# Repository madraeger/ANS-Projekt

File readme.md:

# FM-VCO

Dieses Repository enthält die Entwicklung, Simulation und praktische Umsetzung eines spannungsgesteuerten Oszillators für einen Frequenzmodulator.

Der VCO wird in **KiCad** aufgebaut und mit **ngspice** simuliert. Anschließend soll die Schaltung auf einer Platine umgesetzt und messtechnisch untersucht werden.

## Kundenanforderungen

Für den Frequenzmodulator wurden folgende Anforderungen vorgegeben:

- Mittenfrequenz von **5,5 MHz**
- Eingangssignal von **0 V**
- lineare Frequenzänderung von **±0,5 MHz**
- nutzbarer Frequenzbereich von **5 MHz bis 6 MHz**
- möglichst geringe nichtlineare Verzerrungen
- robuste und übersichtliche Platine für den Einsatz im Unterricht
- Verwendung möglichst großer und gut handhabbarer Bauteile
- integrierter Spannungsteiler zur Einstellung des Arbeitspunktes
- Ein- und Ausgang über BNC-Buchsen
- Ausgangswiderstand von **50 Ω**
- Korrektur einer Frequenzdrift über eine einstellbare Gleichspannung
- Aufnahme der Frequenzkennlinie mithilfe einer Gleichspannung
- möglichst kurzschlusssicherer Ausgang

## Grundlagen und Aufbau des VCOs

### Vom Schwingkreis zum Oszillator

Die Grundlage des VCOs bildet ein LC-Schwingkreis aus Induktivitäten und Kapazitäten. Im Schwingkreis wird Energie periodisch zwischen dem magnetischen Feld der Induktivitäten und dem elektrischen Feld der Kapazitäten ausgetauscht.

Die Resonanzfrequenz kann näherungsweise mit

$$
f_0 \approx \frac{1}{2\pi\sqrt{L_\text{}C_\text{}}}
$$

beschrieben werden.

Dabei sind:

- $L_\text{}$ die wirksame Induktivität des Schwingkreises
- $C_\text{}$ die gesamte wirksame Kapazität einschließlich parasitärer Kapazitäten

Ein realer LC-Schwingkreis besitzt Verluste, beispielsweise durch die Innenwiderstände der Induktivitäten, Leiterbahnen und angeschlossene Messgeräte. Ohne zusätzliche Energiezufuhr würde die Schwingung deshalb mit der Zeit abklingen.

Damit eine dauerhafte Schwingung entsteht, muss eine aktive Schaltung die Verluste des Schwingkreises ausgleichen. Dazu wird ein Teil des Ausgangssignals phasenrichtig zurückgeführt und verstärkt. Beim Einschalten reichen bereits kleine Störungen und das elektrische Rauschen aus, um eine Schwingung anzuregen. Die Frequenzanteile in der Nähe der Resonanzfrequenz werden anschließend durch die Rückkopplung verstärkt.

Für das Anschwingen muss die Schleifenverstärkung zunächst ausreichend groß sein. Im eingeschwungenen Zustand stellt sich die Amplitude so ein, dass die zugeführte Energie den Verlusten des Schwingkreises entspricht.

### Aufbau des VCOs

Der verwendete VCO besteht grundsätzlich aus einem differentiellen LC-Schwingkreis, einem gekreuzt gekoppelten MOSFET-Paar und einer Stromquelle.

<p align="center">
  <em>
    Vereinfachter Aufbau eines differentiellen LC-VCOs.
    Quelle:
    <a href="https://analogcircuitdesign.com/voltage-controlled-oscillator/">
      Analog Circuit Design
    </a>
  </em>
</p>

Der VCO setzt sich aus folgenden Funktionsgruppen zusammen:

| Funktionsgruppe | Bauteile der Prinzipschaltung | Bauteile der aktuellen Schaltung | Aufgabe |
|---|---|---|---|
| LC-Schwingkreis | `L1`, `L2`, `C1`, `C2` sowie die Verlustwiderstände `R1`, `R2` | `L1`, `L2`, `D1`, `D2` | Festlegung der Resonanzfrequenz |
| Cross-Coupled-Paar | `M1`, `M2` | `Q1`, `Q2` | Ausgleich der Schwingkreisverluste und Aufrechterhaltung der Schwingung |
| Frequenzabstimmung | Varaktordioden und Steuerspannung `Vctrl` | `D1`, `D2` und Abstimmspannung `Vtune` | Veränderung der wirksamen Kapazität und damit der Ausgangsfrequenz |
| Stromquelle | ideale Stromquelle `Idc` | `Q3`, `Q4`, `R4` | Einstellung und Begrenzung des Arbeitspunktstroms |
| Ausgang | einer der beiden Schwingkreisknoten | rechter Schwingkreisknoten | Ausgabe des hochfrequenten Signals |

In der Prinzipschaltung werden die Verluste des LC-Schwingkreises durch die Parallelwiderstände `R1` und `R2` dargestellt. In der realen Schaltung entstehen diese Verluste bereits durch die Innenwiderstände der Spulen, die Varaktordioden, die MOSFETs und die Leiterbahnen. Deshalb wurden keine zusätzlichen Widerstände parallel zum Schwingkreis eingesetzt.

Die Kondensatoren `C1` und `C2` der Prinzipschaltung werden in der aktuellen Schaltung hauptsächlich durch die spannungsabhängigen Kapazitäten der Varaktordioden `D1` und `D2` ersetzt.

Der LC-Schwingkreis bestimmt die Ausgangsfrequenz. Das Cross-Coupled-Transistorpaar führt dem Schwingkreis die durch reale Verluste abgegebene Energie wieder zu. Die Varaktordioden ermöglichen die spannungsabhängige Frequenzeinstellung über `Vtune`.

Als Stromquelle wird ein einfacher NMOS-Stromspiegel verwendet. Dieser stellt den Arbeitspunktstrom für das Cross-Coupled-Transistorpaar bereit.

Die einzelnen Funktionsgruppen werden in den folgenden Abschnitten genauer beschrieben.
### Cross-Coupled-Transistorpaar

Die MOSFETs `Q1` und `Q2` sind über Kreuz miteinander gekoppelt. Das Gate eines Transistors ist jeweils mit dem Drain des anderen Transistors verbunden.

Die beiden Schwingkreisknoten schwingen dadurch näherungsweise gegenphasig. Steigt die Spannung an einem Knoten an, fällt sie am anderen Knoten ab.

Das Transistorpaar erzeugt im Schwingkreis einen negativen differentiellen Widerstand. Dieser wirkt den realen Verlustwiderständen des Schwingkreises entgegen. Sind die Verluste ausreichend kompensiert, kann die Schwingung dauerhaft bestehen bleiben.

### Spannungsabhängige Frequenzabstimmung

Damit aus dem LC-Oszillator ein spannungsgesteuerter Oszillator wird, werden die festen Kapazitäten durch Varaktordioden ersetzt.

Eine Varaktordiode wird in Sperrrichtung betrieben und verhält sich dabei wie ein spannungsabhängiger Kondensator. Die Abstimmspannung `Vtune` verändert die Sperrspannung und damit die Kapazität der Dioden.

Dadurch verändert sich die wirksame Kapazität des Schwingkreises:

$$
V_\text{tune}
\longrightarrow
C_\text{Varaktor}
\longrightarrow
f_\text{out}
$$

In der aktuellen Schaltung nimmt die gemessene Ausgangsfrequenz mit zunehmender Spannung `Vtune` ab. Die genaue Richtung der Frequenzänderung hängt von der Verschaltung der Varaktordioden und den Spannungsverhältnissen innerhalb des Schwingkreises ab.

Für einen möglichst verzerrungsarmen Frequenzmodulator sollte der Zusammenhang zwischen Abstimmspannung und Ausgangsfrequenz im verwendeten Arbeitsbereich möglichst linear sein:

$$
f_\text{out}
\approx
f_\text{Mitte}
+
K_\text{VCO}\cdot\left(V_\text{tune}-V_\text{Mitte}\right)
$$

Dabei beschreibt $K_\text{VCO}$ die Empfindlichkeit des VCOs und wird beispielsweise in `MHz/V` angegeben.

### NMOS-Stromspiegel

Die Stromquelle des VCOs wird als einfacher NMOS-Stromspiegel ausgeführt.

<p align="center">
  <em>
    Prinzip eines einfachen NMOS-Stromspiegels.
    Quelle:
    <a href="https://www.allaboutcircuits.com/technical-articles/the-basic-mosfet-constant-current-source/">
      All About Circuits
    </a>
  </em>
</p>

Der Stromspiegel besteht in der aktuellen Schaltung aus den MOSFETs `Q3` und `Q4` sowie dem Widerstand `R4`.

Bei `Q4` sind Gate und Drain miteinander verbunden. Der Transistor ist damit als Referenztransistor beschaltet. Über den Widerstand `R4` stellt sich ein Referenzstrom ein.

Da die Gates von `Q3` und `Q4` miteinander verbunden sind, liegt an beiden MOSFETs näherungsweise dieselbe Gate-Source-Spannung an. Dadurch übernimmt `Q3` näherungsweise den Strom des Referenzzweigs und stellt den Arbeitspunktstrom für das Cross-Coupled-Transistorpaar bereit.

Die Bauteile der Prinzipschaltung entsprechen in der aktuellen VCO-Schaltung folgenden Bauteilen:

| Prinzipschaltung | Aktuelle Schaltung |
|---|---|
| Referenztransistor `Q1` | `Q4` |
| Ausgangstransistor `Q2` | `Q3` |
| Einstellwiderstand `RSET` | `R4` |
| Referenzstrom `IREF` | Strom durch `R4` und `Q4` |
| Ausgangsstrom `IBIAS` | Arbeitspunktstrom für `Q1` und `Q2` |

Der Referenzstrom kann vereinfacht mit folgender Gleichung abgeschätzt werden:

$$
I_\text{REF}
\approx
\frac{V_\text{DD}-V_\text{GS}}{R_4}
$$

Diese Gleichung ist nur eine Näherung, da die Gate-Source-Spannung `VGS` vom verwendeten MOSFET, vom Strom und von der Temperatur abhängt.

Der Stromspiegel stabilisiert damit den Arbeitspunkt der Schaltung, stellt jedoch keine vollständige automatische Regelung der Ausgangsamplitude dar.

## Verwendete Bauteile

Für den aktuellen Aufbau werden unter anderem folgende Bauteile verwendet:

| Bezeichnung | Bauteil | Funktion | SPICE-Modell / Bibliothek | Datenblatt |
|---|---|---|---|---|
| Q1, Q2 | [`BS170`](https://www.onsemi.com/download/data-sheet/pdf/mmbf170-d.pdf) | Cross-Coupled-Transistorpaar | `elk.lib` |  |
| Q3, Q4 | [`BS170`](https://www.onsemi.com/download/data-sheet/pdf/mmbf170-d.pdf) | NMOS-Stromspiegel | `elk.lib` |  |
| D1, D2 | [`1SV149`](https://www.radiomuseum.co.uk/filter/1SV149.pdf) | Varaktordioden zur Frequenzabstimmung | `BB112.lib` beziehungsweise eigenes `1SV149`-Modell |  |
| L1, L2 | 3,3 µH | Induktiver Teil des Schwingkreises | Standardmodell aus `spice.lib` | – |
| R4 | 51 kΩ | Einstellung des Referenzstroms im realen Aufbau | Standardmodell aus `spice.lib` | – |

Für die MOSFETs wird das Modell des `BS170` aus der Bibliothek `elk.lib` verwendet. Die passiven Bauteile greifen auf die Standardmodelle aus `spice.lib` zurück.

Für die Varaktordioden wurde zunächst das Modell aus `BB112.lib` verwendet, da damit in der Simulation eine deutliche Frequenzänderung erreicht werden konnte. Alternativ wird ein eigenes Modell für die `1SV149` eingesetzt. Das Modell aus `BB112.lib` entspricht dabei nicht exakt der real verbauten `1SV149`, sondern dient lediglich als Näherung ihres kapazitätsabhängigen Verhaltens.

## Aktueller Stand

Der VCO wurde sowohl in **SPICE simuliert** als auch **praktisch aufgebaut**. Der geforderte nutzbare Frequenzbereich von ungefähr **5 MHz bis 6 MHz** wird bereits erreicht.

Die Ausgangsfrequenz wird über die Abstimmspannung `Vtune` eingestellt. Mit steigender Abstimmspannung sinkt die Ausgangsfrequenz. Die aufgenommenen Messwerte zeigen dabei einen nahezu linearen Zusammenhang zwischen `Vtune` und der Ausgangsfrequenz.

### Gemessene f/V-Kennlinie

Die Kennlinie wurde aufgenommen, indem die Gleichspannung `Vtune` schrittweise verändert und die jeweilige Ausgangsfrequenz gemessen wurde.

| `Vtune` in V | Frequenz in MHz |
|---:|---:|
| 5,33 | 6,00 |
| 5,50 | 5,90 |
| 5,63 | 5,83 |
| 5,82 | 5,69 |
| 5,92 | 5,61 |
| 6,06 | 5,52 |
| 6,24 | 5,42 |
| 6,36 | 5,33 |
| 6,54 | 5,21 |
| 6,70 | 5,11 |
| 6,89 | 5,01 |

<p align="center">
  <em>Gemessene Ausgangsfrequenz in Abhängigkeit von der Abstimmspannung Vtune</em>
</p>

Die VCO-Empfindlichkeit beträgt näherungsweise:

$$
K_\text{VCO}
\approx
-0{,}650\,
\frac{\text{MHz}}{\text{V}}
$$

Das negative Vorzeichen bedeutet, dass die Ausgangsfrequenz mit steigender Abstimmspannung abnimmt.

Die Mittenfrequenz von ungefähr **5,5 MHz** wird bei einer Abstimmspannung von etwa **6,1 V** erreicht.

Für den gesamten Frequenzbereich von ungefähr **5 MHz bis 6 MHz** wird eine Spannungsänderung von etwa

$$
\Delta V_\text{tune} = 6{,}89\,\text{V} - 5{,}33\,\text{V} = 1{,}56\,\text{V}
$$

benötigt.

Bezogen auf den Arbeitspunkt bei ungefähr **6,1 V** entspricht dies einem benötigten Spannungshub von ungefähr:

$$
V_\text{tune}
\approx
6{,}1\,\text{V}
\pm
0{,}78\,\text{V}
$$

Der ursprünglich vorgesehene Eingangsspannungsbereich von ungefähr **±0,5 V** reicht daher ohne eine zusätzliche Anpassung nicht für den vollständigen Frequenzbereich aus.

### Gemessene Ausgangssignale

Die folgende Abbildunge zeigt die letzten zwei Perioden des mit dem Oszilloskop aufgenommenen Ausgangssignals.

<p align="center">
  <em>Gemessenes Ausgangssignal bei 5 - 6 MHz</em>
</p>

Die gemessenen Signale besitzen über den untersuchten Frequenzbereich eine weitgehend sinusförmige Signalform.

Die Ausgangsamplitude ist bei **5 MHz** und **5,5 MHz** ähnlich groß. In Richtung **6 MHz** nimmt die Amplitude jedoch sichtbar ab. Die Ursache dafür muss im weiteren Projektverlauf noch untersucht werden.

### Simulation und Vergleich

Für die Frequenzen **5 MHz**, **5,5 MHz** und **6 MHz** wurden die simulierten Ausgangssignale mit den Oszilloskopmessungen verglichen.

<details>
  <summary><strong>Vergleich bei 5 MHz anzeigen</strong></summary>

  #### Vergleich bei 5 MHz

</details>

<details>
  <summary><strong>Vergleich bei 5,5 MHz anzeigen</strong></summary>

  #### Vergleich bei 5,5 MHz

</details>

<details>
  <summary><strong>Vergleich bei 6 MHz anzeigen</strong></summary>

  #### Vergleich bei 6 MHz

</details>

Die normierten Vergleichsplots zeigen, dass Simulation und Messung grundsätzlich eine ähnliche periodische Signalform besitzen.

Die Simulation beschreibt damit das grundsätzliche Schwingverhalten, bildet den realen Arbeitspunkt und die tatsächliche Ausgangsamplitude jedoch nur eingeschränkt ab.

### Unterschiede zwischen Simulation und realem Aufbau

Für den NMOS-Stromspiegel werden in der Simulation und im realen Aufbau unterschiedliche Widerstandswerte benötigt.

Im realen Aufbau wird für `R4` ein Widerstand von **51 kΩ** verwendet. Bei größeren Widerständen ist der Strom zu gering, sodass der Oszillator nicht zuverlässig anschwingt.

In der SPICE-Simulation wird dagegen ein größerer Widerstand benötigt, da kleinere Widerstandswerte dort zu stärkeren Verzerrungen des Ausgangssignals führen.

Zusätzlich wurden im realen Aufbau Kondensatoren parallel zur Spannungsversorgung eingesetzt. Diese dienen als Abblock- und Stützkondensatoren und reduzieren hochfrequente Störungen sowie kurzzeitige Spannungsschwankungen.

### Platinenlayout

Eine erste Platine wurde bereits in KiCad erstellt. Das Layout muss jedoch noch an den aktuellen Schaltungsstand angepasst und weiter optimiert werden.

Besonders berücksichtigt werden müssen:

- Platzierung der Abblockkondensatoren nahe an den MOSFETs
- Ein- und Ausgangsanpassung

## Noch nicht vollständig erfüllte Anforderungen

Der geforderte Frequenzbereich von ungefähr **5 MHz bis 6 MHz** und die Mittenfrequenz von ungefähr **5,5 MHz** werden bereits erreicht. Auch die Frequenzkennlinie wurde mithilfe einer veränderlichen Gleichspannung aufgenommen und zeigt im untersuchten Bereich einen nahezu linearen Verlauf.

Folgende Kundenanforderungen sind noch nicht vollständig erfüllt:

- Anpassung des Eingangs von **0 V**
- Umsetzung einer Frequenzänderung von ungefähr **±0,5 MHz** bei einem Eingangssignal von **±0,5 V**
- weitere Verringerung beziehungsweise genaue Bewertung der nichtlinearen Verzerrungen
- Anpassung und Optimierung des bereits erstellten Platinenlayouts
- Realisierung eines Ausgangswiderstands von **50 Ω**
- Umsetzung und Prüfung der Korrektur einer Frequenzdrift über eine einstellbare Gleichspannung
- möglichst kurzschlusssichere Auslegung des Ausgangs
- Aufbau und Prüfung der endgültigen Platine

## Verwendete Software

Für die Entwicklung, Simulation und Versionsverwaltung werden folgende Programme verwendet:

| Software | Verwendung | Download |
|---|---|---|
| KiCad | Erstellung des Schaltplans und des Platinenlayouts |  |
| ngspice | Simulation der Schaltung und Untersuchung des VCO-Verhaltens |  |
| Git | Lokale Versionsverwaltung des Projekts |  |
| GitHub | Speicherung und gemeinsame Bearbeitung des Repositorys |  |

KiCad verwendet für die integrierte SPICE-Simulation ngspice. Abhängig von der KiCad-Installation kann ngspice daher bereits enthalten sein.

## Projekt öffnen

Das Repository kann mit folgendem Befehl geklont werden:

```bash
git clone <URL-DES-REPOSITORY>
```

Der aktuelle Stand des KiCad-Projekts befindet sich im folgenden Unterordner:

```text
kicad/FM-ELK_LC-VCO-V3
```

Anschließend kann die darin enthaltene `.kicad_pro`-Datei mit KiCad geöffnet werden.

Vor der Simulation sollte überprüft werden, ob:

- alle Symbolbibliotheken vorhanden sind
- alle Footprints korrekt zugeordnet sind
- das SPICE-Modell der `1SV149` eingebunden ist
- die Modellpfade in KiCad korrekt eingestellt sind

## Projektteam

<p>

</p>

## Literaturverzeichnis

Die folgenden Quellen wurden für die Grundlagen und die Entwicklung der Schaltung verwendet:

1. [Analog Circuit Design: Voltage Controlled Oscillator – VCO Basics, Operation, Tuning and Use in Communication Circuits](https://analogcircuitdesign.com/voltage-controlled-oscillator/)  
   Grundlagen zu spannungsgesteuerten Oszillatoren, LC-VCOs, Varaktordioden und VCO-Kennlinien.

2. [Electronics Tutorials: LC Oscillator Tutorial and Tuned LC Oscillator Basics](https://www.electronics-tutorials.ws/oscillator/oscillators.html)  
   Grundlagen zu LC-Schwingkreisen, Rückkopplung und den Bedingungen für eine dauerhafte Schwingung.

3. [ElektronikTutor: Frequenzmodulation](https://www.elektroniktutor.de/signalkunde/fm.html)  
   Grundlagen zur Frequenzmodulation, zum Frequenzhub, zum Modulationsindex und zur Bandbreite eines FM-Signals.

4. [All About Circuits: The Basic MOSFET Constant-Current Source](https://www.allaboutcircuits.com/technical-articles/the-basic-mosfet-constant-current-source/)  
   Grundlagen zur MOSFET-Stromquelle und zum Stromspiegel.

Alle Internetquellen wurden zuletzt am **18. Juli 2026** abgerufen.

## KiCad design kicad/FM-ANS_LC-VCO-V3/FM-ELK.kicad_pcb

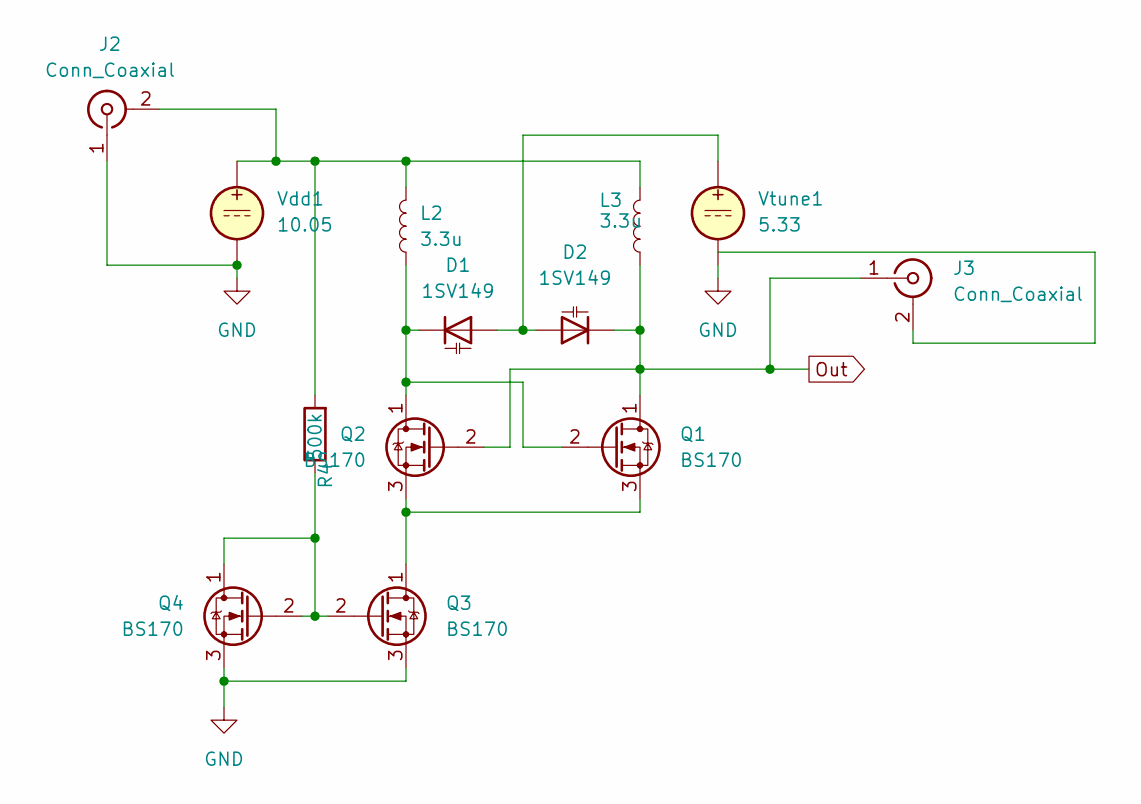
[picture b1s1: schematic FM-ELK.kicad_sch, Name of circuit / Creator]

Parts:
D1, D2: 1SV149; TO-92_Inline
J2, J3: Conn_Coaxial; BNC_Amphenol_031-5539_Vertical
L2, L3: 3.3u; L_Radial_D10.0mm_P5.00mm_Fastron_07P
Q1, Q2, Q3, Q4: BS170; TO-92_Inline
R4: 500k; R_Axial_DIN0207_L6.3mm_D2.5mm_P7.62mm_Horizontal
Vdd1: 10.05; PinHeader_1x02_P2.54mm_Vertical
Vtune1: 5.33; PinHeader_1x02_P2.54mm_Vertical

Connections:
GND: J2.1 (In), Q3.3 (S), Q4.3 (S), Vdd1.2, Vtune1.2
unnamed: D1.2 (A), D2.2 (A), Vtune1.1
unnamed: D1.1 (K), L2.1, Q1.2 (G), Q2.1 (D)
unnamed: J2.2 (Ext), L2.2, L3.2, R4.2, Vdd1.1
unnamed: Q1.3 (S), Q2.3 (S), Q3.1 (D)
unnamed: Q3.2 (G), Q4.1 (D), Q4.2 (G), R4.1
Out: D2.1 (K), J3.1 (In_1), L3.1, Q1.1 (D), Q2.2 (G)

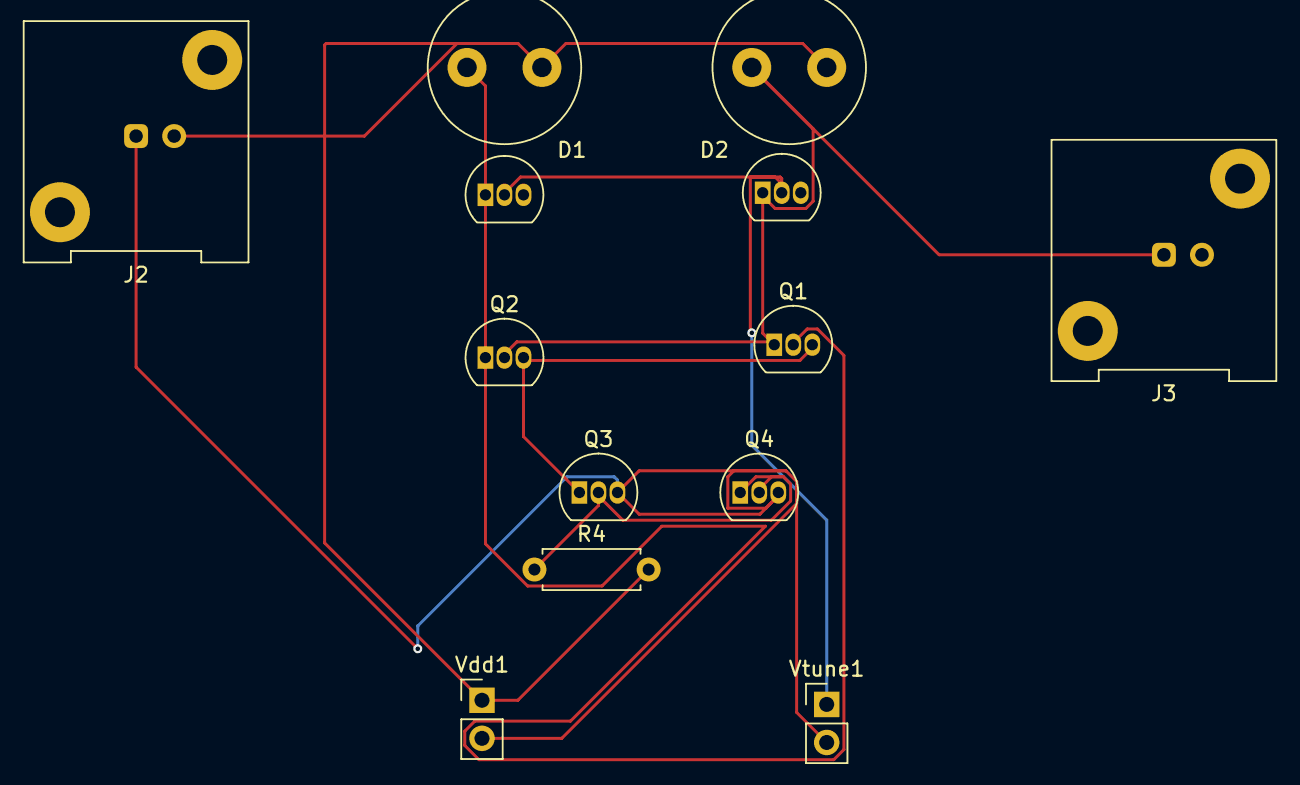
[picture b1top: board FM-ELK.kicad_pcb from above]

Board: 2 copper layers, 13 parts (0 on the bottom side), 7 nets.

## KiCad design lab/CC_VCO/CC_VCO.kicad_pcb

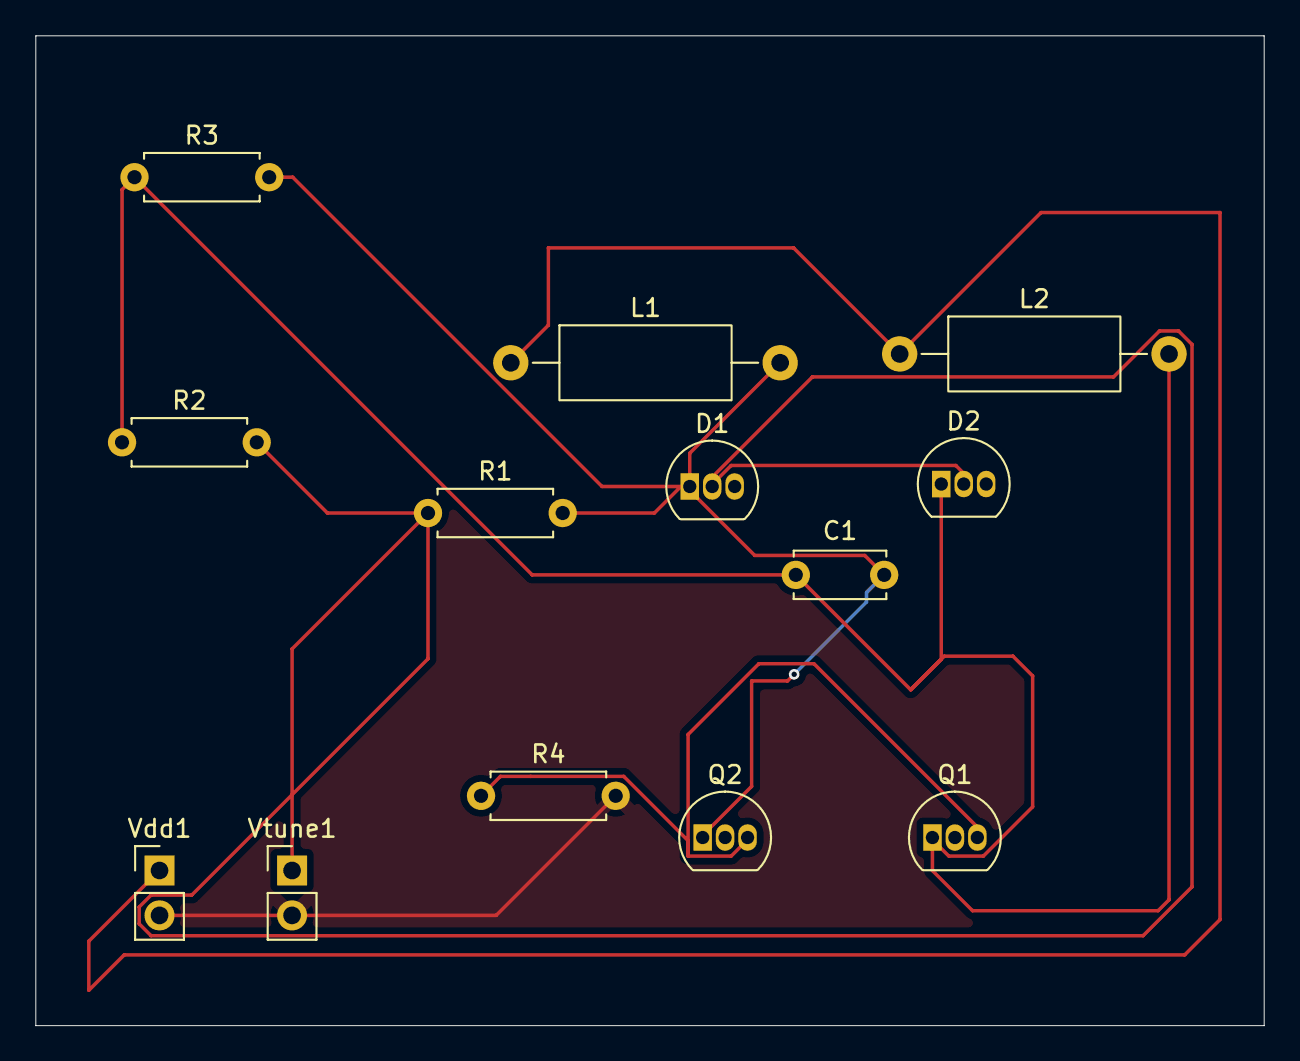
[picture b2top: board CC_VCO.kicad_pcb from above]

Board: 2 copper layers, 69.5 x 56.0 mm, 13 parts (0 on the bottom side), 6 nets.

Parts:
C1: 10p; C_Disc_D5.0mm_W2.5mm_P5.00mm
D1, D2: BB112; TO-92_Inline
L1, L2: 3,3u; L_Axial_L9.5mm_D4.0mm_P15.24mm_Horizontal_Fastron_SMCC
Q1, Q2: BS170; TO-92_Inline
R1, R2, R3: 10k; R_Axial_DIN0207_L6.3mm_D2.5mm_P7.62mm_Horizontal
R4: 25.5k; R_Axial_DIN0207_L6.3mm_D2.5mm_P7.62mm_Horizontal
Vdd1: 10; PinHeader_1x02_P2.54mm_Vertical
Vtune1: 1; PinHeader_1x02_P2.54mm_Vertical

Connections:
/Vd2: C1.2, D1.1 (K), L1.2, Q2.1 (D), R1.2, R3.2
/Vdd: L1.1, L2.1, Vdd1.1
/Vtune: D1.2 (A), D2.2 (A), R1.1, R2.2, Vtune1.1
GND: R4.2, Vdd1.2, Vtune1.2
unnamed: Q1.3 (S), Q2.3 (S), R4.1
Out: C1.1, D2.1 (K), L2.2, Q1.1 (D), R2.1, R3.1

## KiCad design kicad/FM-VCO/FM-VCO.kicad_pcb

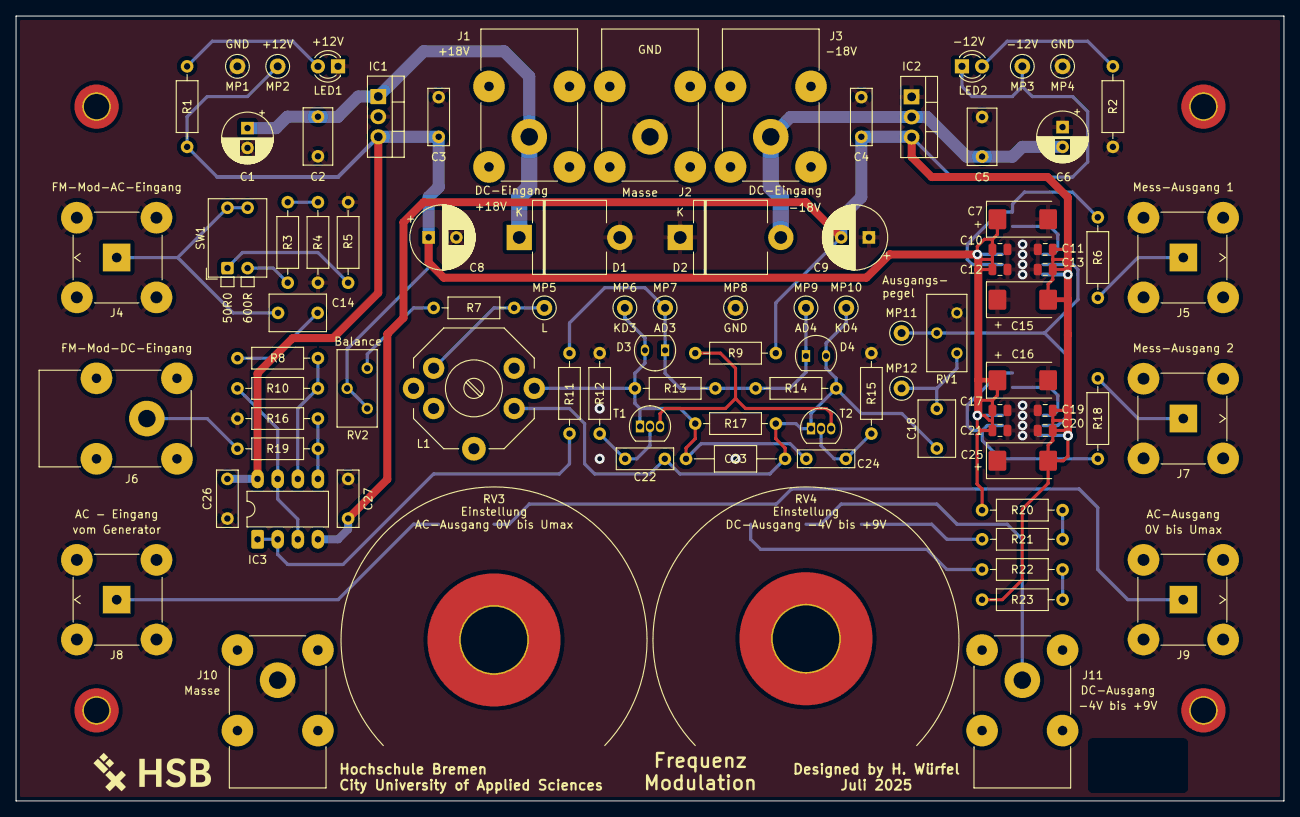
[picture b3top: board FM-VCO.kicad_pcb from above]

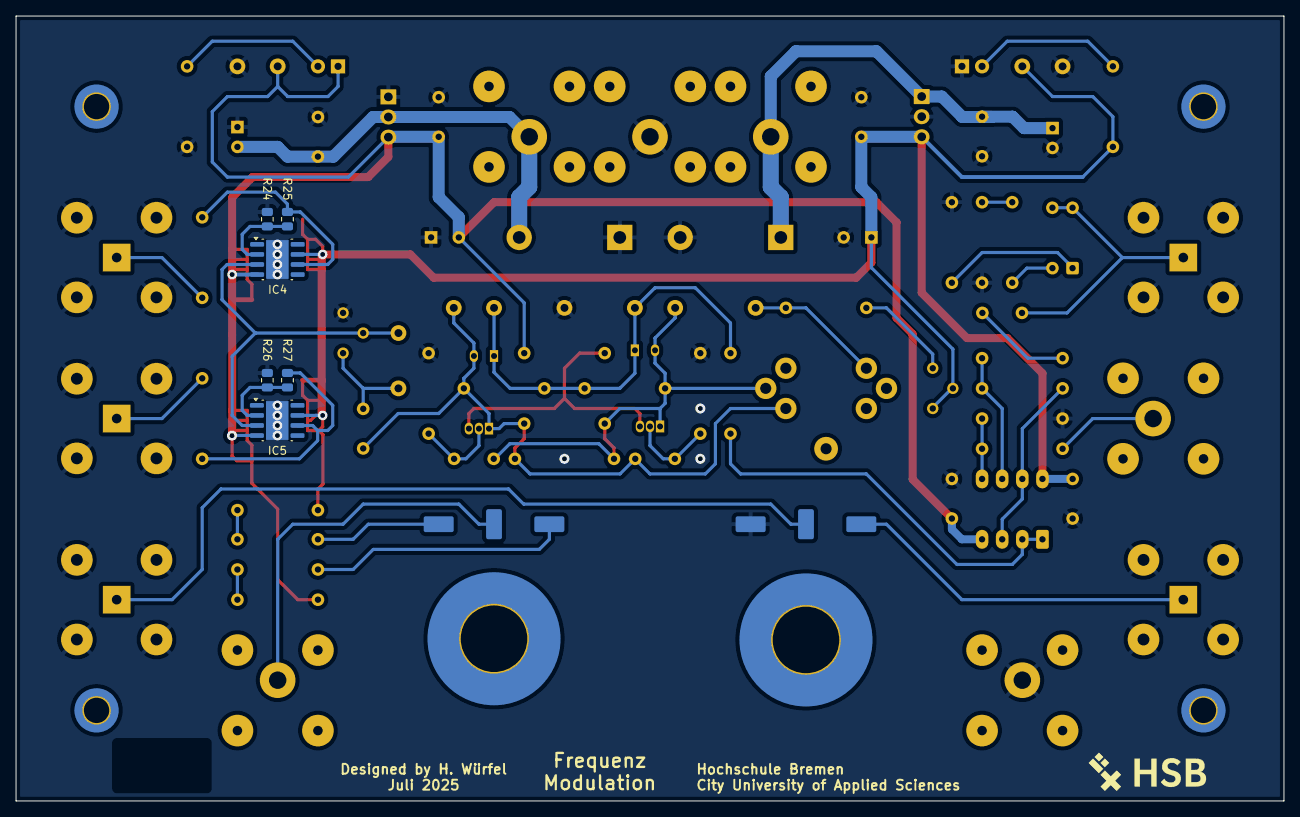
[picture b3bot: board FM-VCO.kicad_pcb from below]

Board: 2 copper layers, 160.0 x 99.1 mm, 104 parts (7 on the bottom side), 40 nets.

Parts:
C1, C6: 10µ; CP_Radial_D6.3mm_P2.50mm
C2, C5: 330n; C_Rect_L7.0mm_W3.5mm_P5.00mm
C3, C4, C26, C27: 100n; C_Rect_L7.0mm_W2.5mm_P5.00mm
C7, C15, C16, C25: 10µ; CP_EIA-7343-31_Kemet-D_Pad2.25x2.55mm_HandSolder
C8, C9: 100µ; CP_Radial_D8.0mm_P3.50mm
C10, C13, C17, C20: 1n; C_0805_2012Metric
C11, C12, C19, C21: 47n; C_0805_2012Metric
C14, C18: 1µ0; C_Rect_L7.0mm_W4.5mm_P5.00mm
C22: 22n; C_Rect_L7.0mm_W2.5mm_P5.00mm
C23: 68p; C_Axial_L5.1mm_D3.1mm_P12.50mm_Horizontal
C24: 22n; C_Rect_L7.0mm_W2.0mm_P5.00mm
D1, D2: P600G; D_P600_R-6_P12.70mm_Horizontal
D3, D4: BB112
G*: LOGO; HSB-Logo
G*#2: LOGO; HSB-Logo
H1, H2, H5, H6: MountingHole; MountingHole_3.2mm_M3_DIN965_Pad_TopBottom
H3, H4: MountingHole; MountingHole_8.4mm_M8_Pad_TopBottom
IC1: LM7812_TO220; TO-220-3_Vertical
IC2: LM7912_TO220; TO-220-3_Vertical
IC3: TL082; DIP-8_W7.62mm_LongPads
IC4, IC5: THS3091DDAR; Texas_R-PDSO-G8_EP2.95x4.9mm_Mask2.4x3.1mm
J1: +18V; Banana_Cliff_FCR7350B_S16N-PC_Horizontal_modi
J2, J10: GND; Banana_Cliff_FCR7350B_S16N-PC_Horizontal_modi
J3: -18V; Banana_Cliff_FCR7350B_S16N-PC_Horizontal_modi
J4: FM-Mod-AC-Eingang; BNC_TEConnectivity_1478035_Horizontal
J5: Mess-Ausgang 1; BNC_TEConnectivity_1478035_Horizontal
J6: FM-Mod-DC-Eingang; Banana_Cliff_FCR7350B_S16N-PC_Horizontal_modi
J7: Mess-Ausgang 2; BNC_TEConnectivity_1478035_Horizontal
J8: AC - Eingang; BNC_TEConnectivity_1478035_Horizontal
J9: AC-Ausgang; BNC_TEConnectivity_1478035_Horizontal
J11: DC-Ausgang; Banana_Cliff_FCR7350B_S16N-PC_Horizontal_modi
L1: 7µ 7µ; Spule_Vielstedter_14mm
LED1, LED2: gn; LED_D3.0mm_Clear
MP1, MP4, MP8: GND; TestPoint_Loop_D2.50mm_Drill1.0mm
MP2: +12V; TestPoint_Loop_D2.50mm_Drill1.0mm
MP3: -12V; TestPoint_Loop_D2.50mm_Drill1.0mm
MP5: L; TestPoint_Loop_D2.50mm_Drill1.0mm
MP6: KD3; TestPoint_Loop_D2.50mm_Drill1.0mm
MP7: AD3; TestPoint_Loop_D2.50mm_Drill1.0mm
MP9: AD4; TestPoint_Loop_D2.50mm_Drill1.0mm
MP10: KD4; TestPoint_Loop_D2.50mm_Drill1.0mm
MP11: U-Treiber-In; TestPoint_Loop_D2.50mm_Drill1.0mm
MP12: Pegel; TestPoint_Loop_D2.50mm_Drill1.0mm
R1, R2: 470R; R_Axial_DIN0207_L6.3mm_D2.5mm_P10.16mm_Horizontal
R3: 590R; R_Axial_DIN0207_L6.3mm_D2.5mm_P10.16mm_Horizontal
R4: 10R0; R_Axial_DIN0207_L6.3mm_D2.5mm_P10.16mm_Horizontal
R5, R6, R18: 50R0; R_Axial_DIN0207_L6.3mm_D2.5mm_P10.16mm_Horizontal
R7: 3K3; R_Axial_DIN0207_L6.3mm_D2.5mm_P10.16mm_Horizontal
R8, R9, R10, R12, R15, R16, R19: 10K0; R_Axial_DIN0207_L6.3mm_D2.5mm_P10.16mm_Horizontal
R11: 4K7; R_Axial_DIN0207_L6.3mm_D2.5mm_P10.16mm_Horizontal
R13, R14: 22K0; R_Axial_DIN0207_L6.3mm_D2.5mm_P10.16mm_Horizontal
R17: 1M0; R_Axial_DIN0207_L6.3mm_D2.5mm_P10.16mm_Horizontal
R20: 1K1; R_Axial_DIN0207_L6.3mm_D2.5mm_P10.16mm_Horizontal
R21: 39R0; R_Axial_DIN0207_L6.3mm_D2.5mm_P10.16mm_Horizontal
R22: 300R; R_Axial_DIN0207_L6.3mm_D2.5mm_P10.16mm_Horizontal
R23: 2K7; R_Axial_DIN0207_L6.3mm_D2.5mm_P10.16mm_Horizontal
R24, R25, R26, R27: 1K2; R_0805_2012Metric
RV1: 20K0; Potentiometer_Bourns_3296Y_Vertical
RV2: 1K0; Potentiometer_Bourns_3296Y_Vertical
RV3: 5K0; Taiss_10Gang_Poti
RV4: 5k0; Taiss_10Gang_Poti
SW1: SW_DIP_x02; SW_DIP_SPSTx02_Piano_CTS_Series194-2MSTN_W7.62mm_P2.54mm
T1, T2: BC546B; TO-92_Inline

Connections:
+12V: C3.1, C7.1, C8.1, C10.1, C12.1, C16.1, C17.2, C21.2, C26.1, IC1.3 (VO), IC3.8 (V+), IC4.7 (V+), IC5.7 (V+), MP2.1, R1.1, R20.2, RV2.1, RV2.2
-12V: C4.2, C9.2, C11.2, C13.2, C15.2, C19.2, C20.2, C25.2, C27.1, IC2.3 (VO), IC3.4 (V-), IC4.4 (V-), IC5.4 (V-), LED2.1 (K), MP3.1, R9.1, R23.2
/FM-Spannungsversorgung/+18V: C1.1, C2.1, D1.1 (K), IC1.1 (VI), J1.1
/FM-Spannungsversorgung/-18V: C5.2, C6.2, D2.2 (A), IC2.2 (VI), J3.1
/IN: IC4.3 (+), IC5.3 (+), MP11.1, RV1.2
/OUT-1: J5.1 (In), R6.2
/OUT-2: J7.1 (In), R18.2
GND: C1.2, C2.2, C3.2, C4.1, C5.1, C6.1, C7.2, C8.2, C9.1, C10.2, C11.1, C12.2, C13.1, C15.1, C16.2, C17.1, C19.1, C20.1, C21.1, C25.1, C26.2, C27.2, D1.2 (A), D2.1 (K), IC1.2 (GND), IC2.1 (GND), IC4.9 (EP), IC5.9 (EP), J2.1, J4.2 (Ext), J5.2 (Ext), J7.2 (Ext), J8.2 (Ext), J9.2 (Ext), J10.1, LED1.1 (K), MP1.1, MP4.1, MP8.1, R2.1, R4.2, R5.2, R12.1, R15.1, R16.2, R24.1, R26.1, RV1.3, RV3.3
unnamed: C14.2, R8.1
unnamed: D3.2 (A), D4.2 (A), MP7.1, MP9.1, R11.1, R13.1, R14.2
unnamed: C23.1, C24.1, D3.1 (K), L1.2, MP6.1, R13.2, R17.1, T1.1 (C)
unnamed: C18.1, C22.2, C23.2, D4.1 (K), L1.3, MP10.1, R14.1, R17.2, T2.1 (C)
unnamed: IC3.3 (+), IC3.7, R10.2
unnamed: IC3.1, IC3.2 (-), R11.2
unnamed: IC3.5 (+), R16.1, R19.2
unnamed: IC3.6 (-), R8.2, R10.1
unnamed: IC4.2 (-), R24.2, R25.1
unnamed: IC4.6, R6.1, R25.2
unnamed: IC5.2 (-), R26.2, R27.1
unnamed: IC5.6, R18.1, R27.2
unnamed: C14.1, J4.1 (In), SW1.3, SW1.4
unnamed: J6.1, R19.1
unnamed: J8.1 (In), RV3.1
unnamed: J9.1 (In), RV3.2
unnamed: J11.1, RV4.2
unnamed: LED1.2 (A), R1.2
unnamed: LED2.2 (A), R2.2
unnamed: L1.6, MP5.1, R7.2
unnamed: C18.2, MP12.1, RV1.1
unnamed: R3.1, SW1.2
unnamed: R3.2, R4.1
unnamed: R5.1, SW1.1
unnamed: R7.1, RV2.3
unnamed: R20.1, R21.2
unnamed: R21.1, RV4.1
unnamed: R22.1, RV4.3
unnamed: R22.2, R23.1
unnamed: C22.1, R12.2, T1.2 (B)
unnamed: R9.2, T1.3 (E), T2.3 (E)
unnamed: C24.2, R15.2, T2.2 (B)

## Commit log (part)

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2026-04-16 Added report and kicad fm-vco
2026-04-16 Added gitignore
2026-04-16 Cleaned file
2026-04-16 Add updated project files
2026-05-07 Laborübungen und Dokumentation hinzugefügt
2026-05-21 Added varactor diodes
2026-06-03 VCO 03.03.26
2026-06-03 CC-VCO Schematic und Quarto doku angepasst
2026-06-10 Bericht angepasst
2026-06-10 Platine erstellt
2026-06-11 Platine aktualisiert
2026-06-11 Schematic update
